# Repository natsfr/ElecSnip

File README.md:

# ElecSnip
Electronic Snippet
Storing all idea/crap/piece/circuit/thought

No interest for anyone else.

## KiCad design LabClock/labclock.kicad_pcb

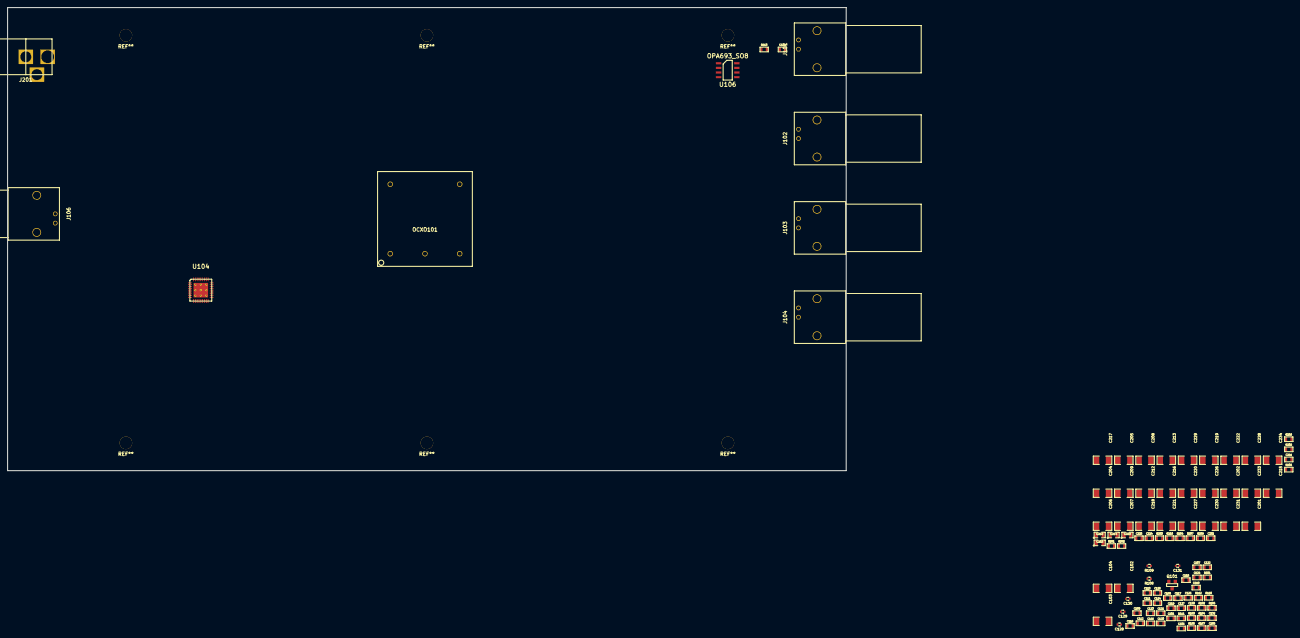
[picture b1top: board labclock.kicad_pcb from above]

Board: 2 copper layers, 230.0 x 127.0 mm, 101 parts (0 on the bottom side), 27 nets, no tracks yet.

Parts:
C101: 1uF; SM0603
C102, C103, C104, C205, C207, C208, C209, C217, C220, C221, C222: 10uF; SM1206
C105: 2uF; SM0603
C106, C109, C110, C111, C112, C116, C119, C121, C123, C124, C127, C133: 100nF; SM0603
C107, C114, C115, C118, C120, C122, C125, C126: 10pF; SM0603
C108, C113, C117: 120pF; SM0603
C128: 1nF; SM0402
C129: 100pF; SM0402
C130, C131: CAP_0402; SM0402
C132: 100pF; SM0603
C134: 10nF; SM0603
C201, C202: 1uF; SM1206
C203, C210, C214, C223: 100nF; SM0805
C204, C206, C212, C213, C215, C216, C218, C219, C226, C227, C228, C229, C230, C231, C233, C234: 10u; SM1206
C211, C224, C225, C232: 1nF; SM0603
J101, J102, J103, J104, J106: BNC; BNC_RHT-610-0048
J201: PJ-002BH-SMT; 2.1mm_DC_Jack_NEB21R_circlehole
OCXO101: NDK_NH26M26LG
Q101: BSS138; SOT23
R101, R111, R112: 1k; SM0603
R102, R103: 100; SM0603
R104: 6k; SM0603
R105, R201, R202, R204, R205, R206, R207, R209, R210: 10k; SM0603
R106: NC; SM0603
R107, R110: 500; SM0603
R108, R109: RES_0402; SM0402
R113: 50; SM0603
R203, R208: 59k; SM0603
U104: STM32F103TB-QFN36; QFN36_6x6_0.5mm
U106: OPA693_SO8; SOIC_8_150mil

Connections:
5V3_OCXO: C203.1, C204.1, C205.1, C206.1, C207.1, R203.2
5V3_PLL: C214.1, C215.1, C216.1, C217.1, C218.1, C219.1, C220.1, C230.1, C231.1, R208.2
5V_AMP: C233.1, C234.1, R111.1, U106.7
5V_OCXO: C101.1, C102.1, C104.1, C212.1, C213.1, OCXO101.5, R101.2
5V_PLL: C106.1, C107.1, C116.1, C118.1, C119.1, C120.1, C121.1, C122.1, C226.1, C228.1
+3.3V: C109.1, C110.1, C111.1, C112.1, C123.1, C124.1, C227.1, C229.1, U104.1, U104.6, U104.19, U104.27
+12V: C103.1, C202.1, C208.1, C209.1, C221.1, C222.1
/MUXOUT: R104.2, R105.1
/OCXO_PW_EN: R201.1, R204.1, R205.1, R206.1, R209.1, R210.1, U104.7
/PLLIN: C132.1, R106.2, R107.2, R110.1
/PLL_VC: C130.1, R109.1
/SINE2AMP: C117.2, C133.1, R106.1
/~PLLSEL: Q101.1, U104.8
GND: C101.2, C102.2, C103.2, C104.2, C105.2, C106.2, C107.2, C109.2, C110.2, C111.2, C112.2, C113.2, C114.1, C115.2, C116.2, C118.2, C119.2, C120.2, C121.2, C122.2, C123.2, C124.2, C125.1, C126.2, C127.2, C129.2, C130.2, C131.2, C201.2, C202.2, C203.2, C204.2, C205.2, C206.2, C207.2, C208.2, C209.2, C211.2, C212.2, C213.2, C214.2, C215.2, C216.2, C217.2, C218.2, C219.2, C220.2, C221.2, C222.2, C224.2, C225.2, C226.2, C227.2, C228.2, C229.2, C230.2, C231.2, C232.2, C233.2, C234.2, J101.2, J101.3, J102.2, J102.3, J103.2, J103.3, J104.2, J104.3, J106.2, J106.3, J201.2, J201.3, OCXO101.2, Q101.2, R103.2, R105.2, R108.2, R110.2, R112.2, R201.2, R202.2, R204.2, R205.2, R206.2, R207.2, R209.2, R210.2, U104.5, U104.18, U104.26, U104.36, U104.37, U106.4
unnamed: C105.1, R102.1
unnamed: C108.1, OCXO101.1, R107.1
unnamed: C114.2, U104.2
unnamed: C115.1, U104.3
unnamed: C128.2, J106.1
unnamed: C131.1, R109.2
unnamed: C133.2, R111.2, R112.1, U106.3
unnamed: C134.1, R113.2
unnamed: C134.2, J101.1
unnamed: C201.1, J201.1
unnamed: R113.1, U106.6
unnamed: R202.1, R203.1
unnamed: R207.1, R208.1

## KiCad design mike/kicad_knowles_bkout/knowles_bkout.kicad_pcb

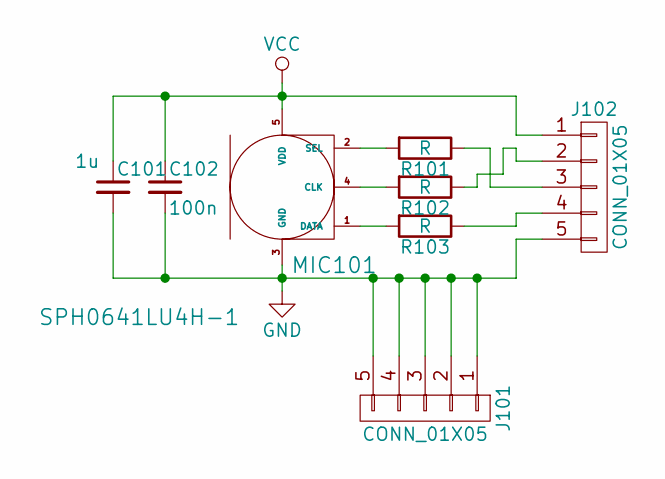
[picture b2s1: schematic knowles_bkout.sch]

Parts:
C101: 1u; C_0805_HandSoldering
C102: 100n; C_0805_HandSoldering
J101, J102: CONN_01X05; Pin_Header_Straight_1x05_Pitch2.54mm
MIC101: SPH0641LU4H-1
R101, R102, R103: R; R_0603_HandSoldering

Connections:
GND: C101.2, C102.2, J101.1, J101.2, J101.3, J101.4, J101.5, J102.5, MIC101.3 (GND)
unnamed: J102.2, R102.1
unnamed: J102.3, R101.1
unnamed: J102.4, R103.1
unnamed: MIC101.1 (DATA), R103.2
unnamed: MIC101.2 (SEL), R101.2
unnamed: MIC101.4 (CLK), R102.2
VCC: C101.1, C102.1, J102.1, MIC101.5 (VDD)

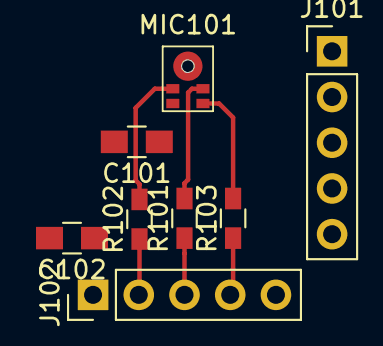
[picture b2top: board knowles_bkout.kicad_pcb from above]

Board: 2 copper layers, 8 parts (0 on the bottom side), 8 nets.

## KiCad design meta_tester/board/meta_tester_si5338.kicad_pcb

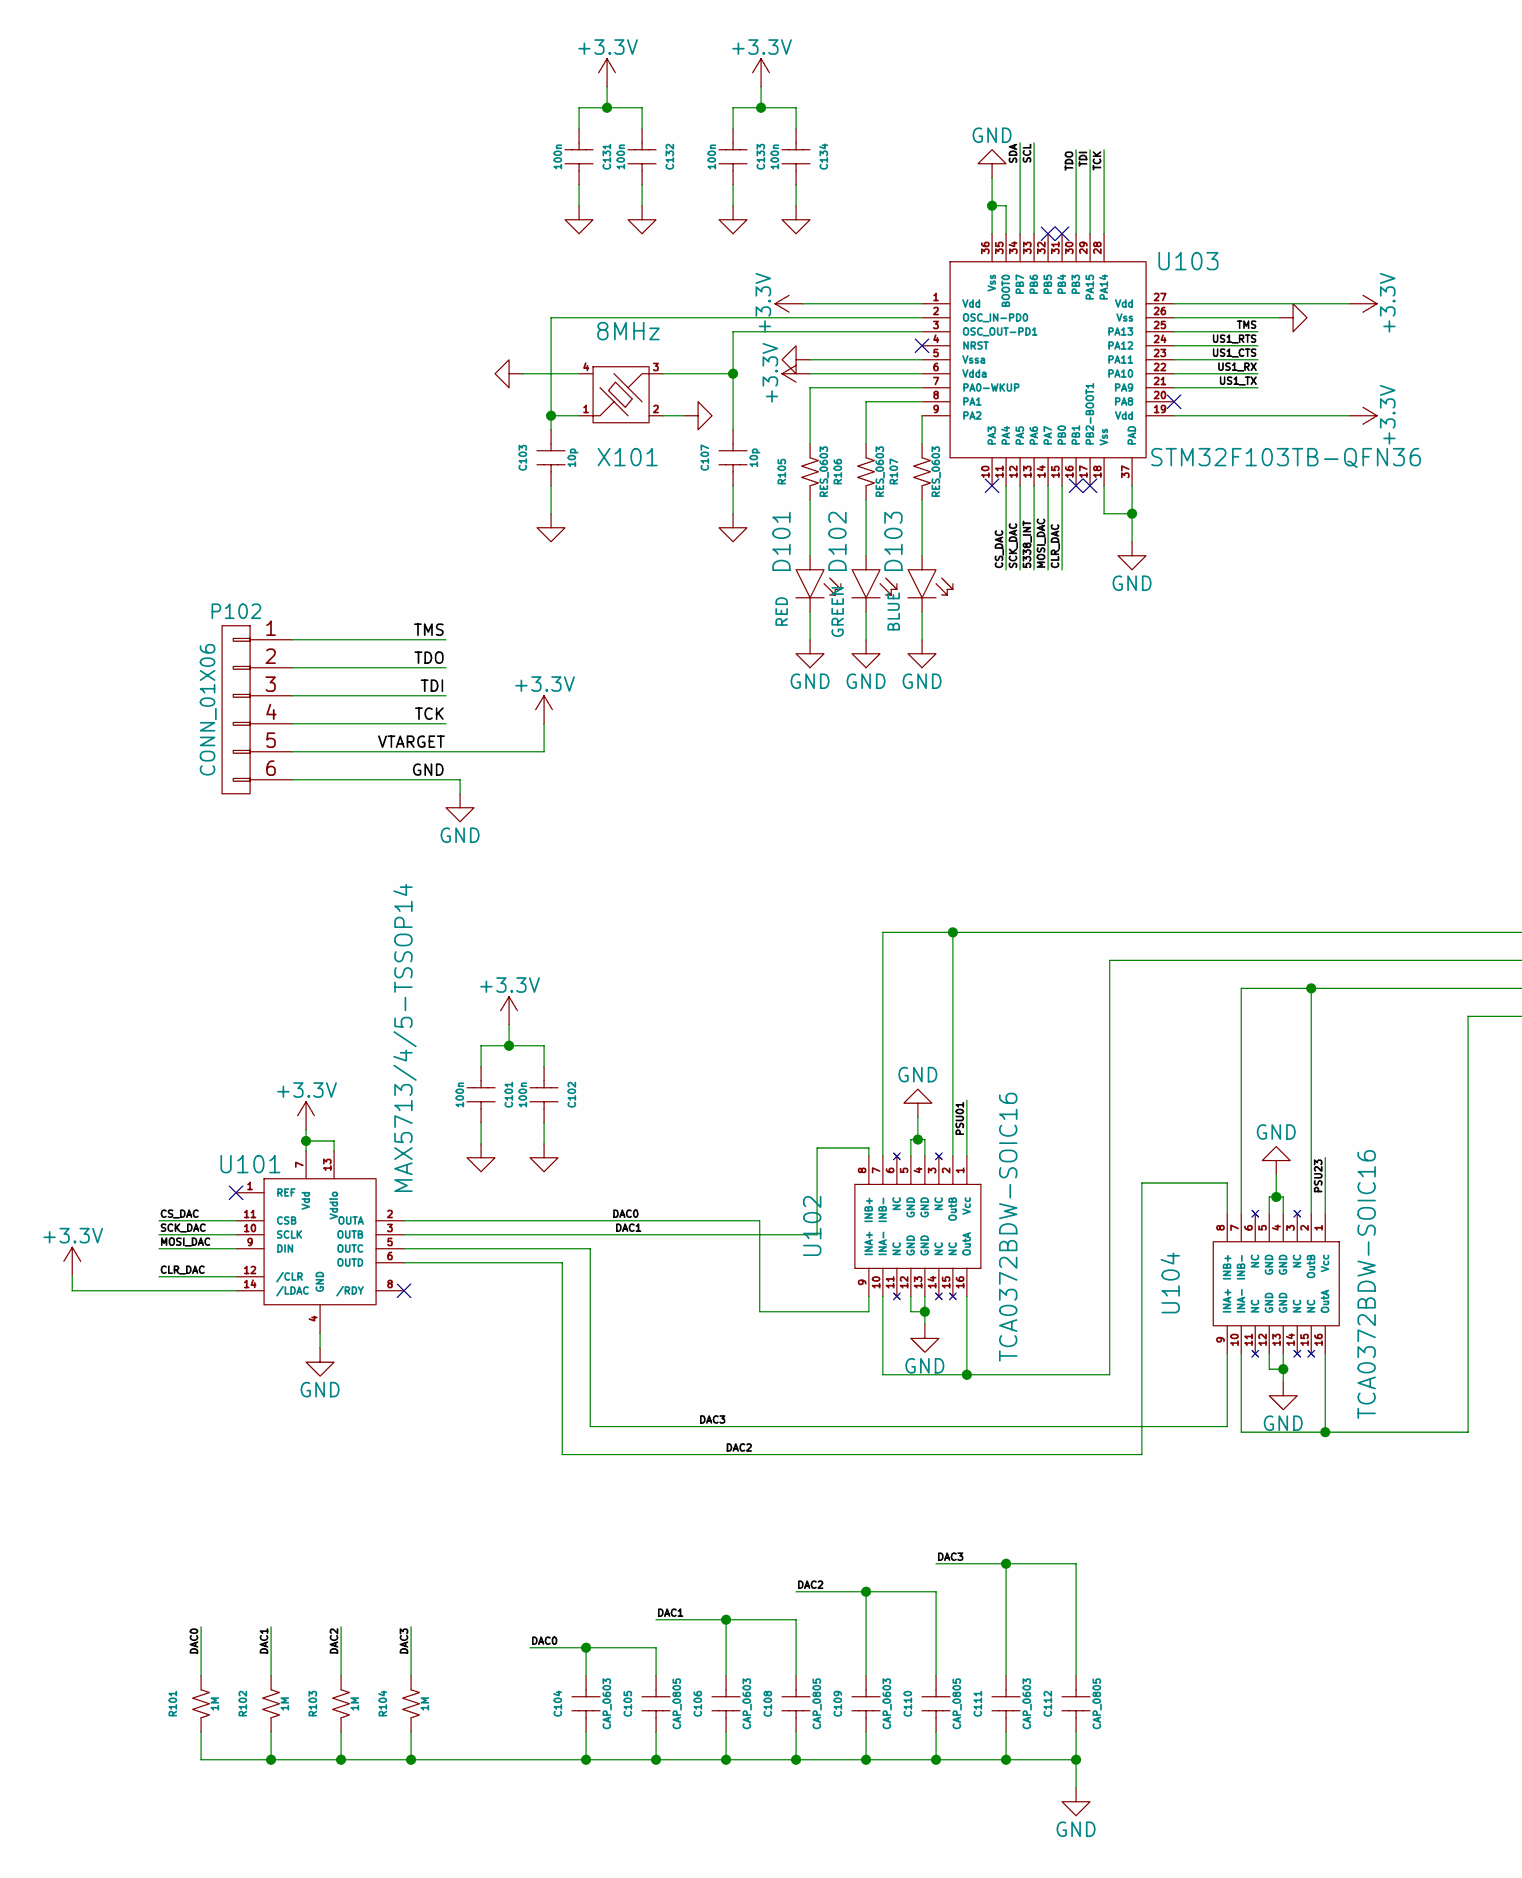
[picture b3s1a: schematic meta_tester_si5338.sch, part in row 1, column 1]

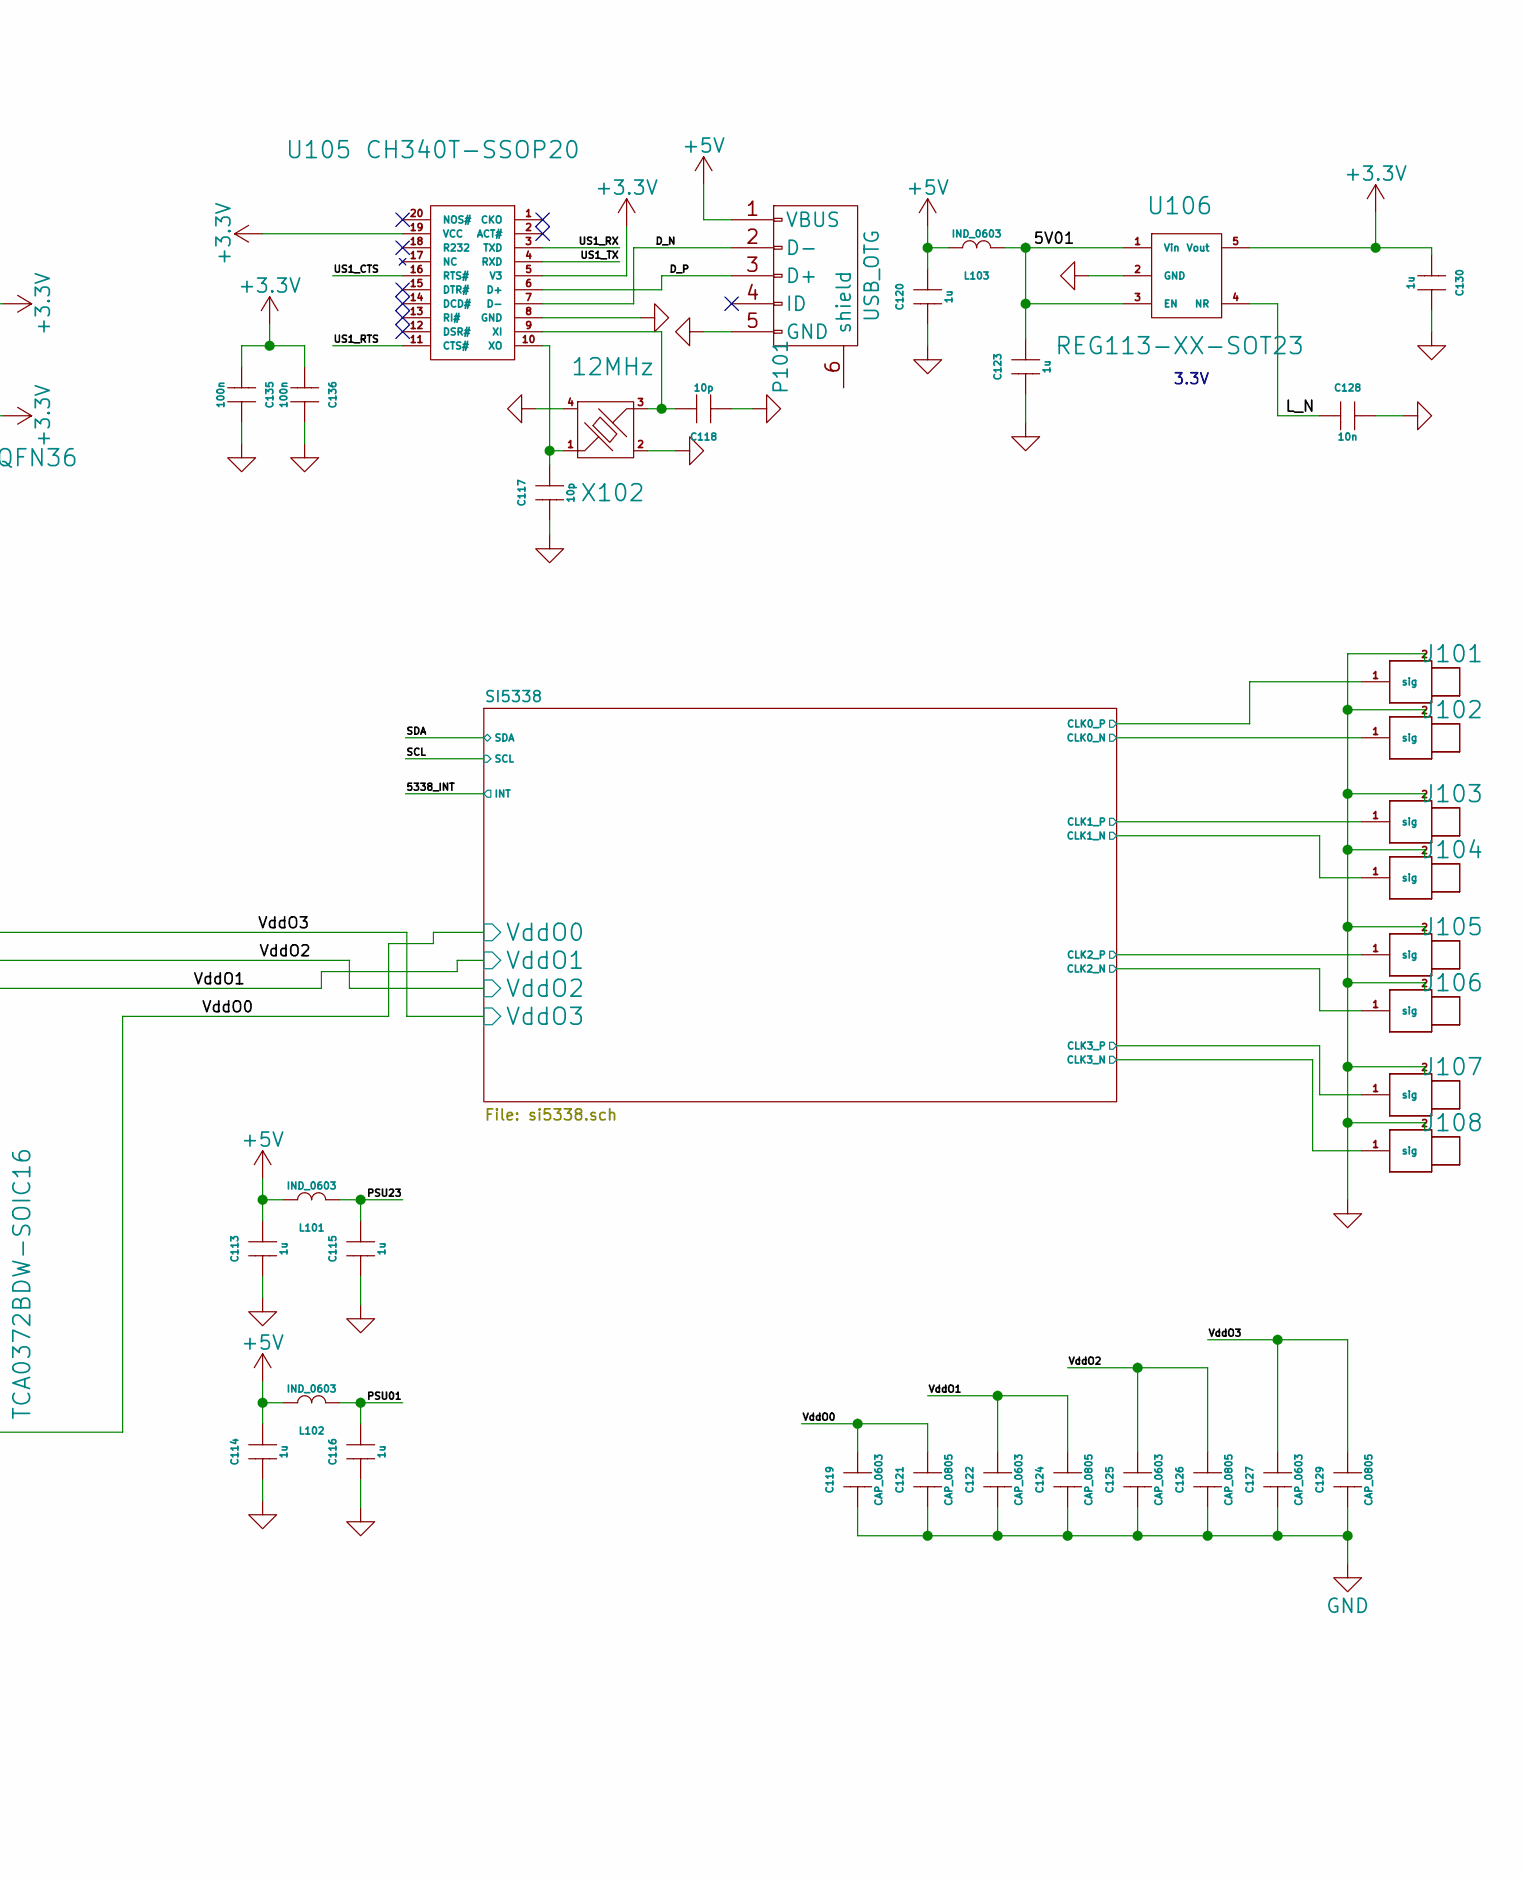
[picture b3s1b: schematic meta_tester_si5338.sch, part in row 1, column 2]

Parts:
C101, C102, C131, C132, C133, C134, C135, C136: 100n; SM0805
C103, C107, C117, C118: 10p; SM0603
C104, C106, C109, C111, C119, C122, C125, C127: CAP_0603; SM0603
C105, C108, C110, C112, C121, C124, C126, C129: CAP_0805; SM0805
C113, C114, C115, C116, C120, C123, C130: 1u; SM0805
C128: 10n; SM0603
D101: RED; LED-0603
D102: GREEN; LED-0603
D103: BLUE; LED-0603
J101, J102, J103, J104, J105, J106, J107, J108: SMA_PCB; SMA_AMP_132322
L101, L102, L103: IND_0603; SM0603
P101: USB_OTG; USB_Mini-B
P102: CONN_01X06; pin_array_6x1
R101, R102, R103, R104: 1M; SM0603
R105, R106, R107: RES_0603; SM0603
U101: MAX5713/4/5-TSSOP14; SSOP14
U102, U104: TCA0372BDW-SOIC16; SOIC-16-10.3x7.5
U103: STM32F103TB-QFN36; QFN36_6x6_0.5mm
U105: CH340T-SSOP20; SSOP-20
U106: REG113-XX-SOT23; SOT23-5
X101: 8MHz; xtal_3.2x2.5
X102: 12MHz; xtal_3.2x2.5

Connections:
+3V3: C101.2, C102.2, C130.2, C131.2, C132.2, C133.2, C134.2, C135.2, C136.2, P102.5, U101.7 (Vdd), U101.13 (Vddio), U101.14 (/LDAC), U103.1 (Vdd), U103.6 (Vdda), U103.19 (Vdd), U103.27 (Vdd), U105.5 (V3), U105.19 (VCC), U106.5 (Vout); also elsewhere on the board
+5V: C113.1, C114.1, C120.1, L101.1, L102.1, L103.1, P101.1 (VBUS)
/5V01: C123.1, L103.2, U106.1 (Vin), U106.3 (EN)
/5338_INT: U103.13 (PA6); also elsewhere on the board
/CLR_DAC: U101.12 (/CLR), U103.15 (PB0)
/CS_DAC: U101.11 (CSB), U103.11 (PA4)
/DAC0: C104.1, C105.1, R101.1, U101.2 (OUTA), U102.9 (INA+)
/DAC1: C106.1, C108.1, R102.1, U101.3 (OUTB), U102.8 (INB+)
/DAC2: C109.1, C110.1, R103.1, U101.6 (OUTD), U104.8 (INB+)
/DAC3: C111.1, C112.1, R104.1, U101.5 (OUTC), U104.9 (INA+)
/D_N: P101.2 (D-), U105.7 (D-)
/D_P: P101.3 (D+), U105.6 (D+)
/L_N: C128.2, U106.4 (NR)
/MOSI_DAC: U101.9 (DIN), U103.14 (PA7)
/PSU01: C116.1, L102.2, U102.1 (Vcc)
/PSU23: C115.1, L101.2, U104.1 (Vcc)
/SCK_DAC: U101.10 (SCLK), U103.12 (PA5)
/SCL: U103.33 (PB6); also elsewhere on the board
/SDA: U103.34 (PB7); also elsewhere on the board
/SI5338/CLK0_N: J102.1 (sig); also elsewhere on the board
/SI5338/CLK0_P: J101.1 (sig); also elsewhere on the board
/SI5338/CLK1_N: J104.1 (sig); also elsewhere on the board
/SI5338/CLK1_P: J103.1 (sig); also elsewhere on the board
/SI5338/CLK2_N: J106.1 (sig); also elsewhere on the board
/SI5338/CLK2_P: J105.1 (sig); also elsewhere on the board
/SI5338/CLK3_N: J108.1 (sig); also elsewhere on the board
/SI5338/CLK3_P: J107.1 (sig); also elsewhere on the board
/TCK: P102.4, U103.28 (PA14)
/TDI: P102.3, U103.29 (PA15)
/TDO: P102.2, U103.30 (PB3)
/TMS: P102.1, U103.25 (PA13)
/US1_CTS: U103.23 (PA11), U105.16 (RTS#)
/US1_RTS: U103.24 (PA12), U105.11 (CTS#)
/US1_RX: U103.22 (PA10), U105.3 (TXD)
/US1_TX: U103.21 (PA9), U105.4 (RXD)
/VddO0: C119.1, C121.1, U104.10 (INA-), U104.16 (OutA); also elsewhere on the board
/VddO1: C122.1, C124.1, U104.2 (OutB), U104.7 (INB-); also elsewhere on the board
/VddO2: C125.1, C126.1, U102.10 (INA-), U102.16 (OutA); also elsewhere on the board
/VddO3: C127.1, C129.1, U102.2 (OutB), U102.7 (INB-); also elsewhere on the board
GND: C101.1, C102.1, C103.2, C104.2, C105.2, C106.2, C107.2, C108.2, C109.2, C110.2, C111.2, C112.2, C113.2, C114.2, C115.2, C116.2, C117.2, C118.2, C119.2, C120.2, C121.2, C122.2, C123.2, C124.2, C125.2, C126.2, C127.2, C128.1, C129.2, C130.1, C131.1, C132.1, C133.1, C134.1, C135.1, C136.1, D101.K, D102.K, D103.K, J101.2, J102.2, J103.2, J104.2, J105.2, J106.2, J107.2, J108.2, P101.5 (GND), P102.6, R101.2, R102.2, R103.2, R104.2, U101.4 (GND), U102.4 (GND), U102.5 (GND), U102.12 (GND), U102.13 (GND), U103.5 (Vssa), U103.18 (Vss), U103.26 (Vss), U103.35 (BOOT0), U103.36 (Vss), U103.37 (PAD), U104.4 (GND), U104.5 (GND), U104.12 (GND), U104.13 (GND), U105.8 (GND), U106.2 (GND), X101.2, X101.4, X102.2, X102.4; also elsewhere on the board
unnamed: C103.1, U103.2 (OSC_IN-PD0), X101.1
unnamed: C107.1, U103.3 (OSC_OUT-PD1), X101.3
unnamed: C117.1, U105.10 (XO), X102.1
unnamed: C118.1, U105.9 (XI), X102.3
unnamed: D101.A, R105.2
unnamed: D102.A, R106.2
unnamed: D103.A, R107.2
unnamed: R105.1, U103.7 (PA0-WKUP)
unnamed: R106.1, U103.8 (PA1)
unnamed: R107.1, U103.9 (PA2)

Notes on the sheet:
3.3V

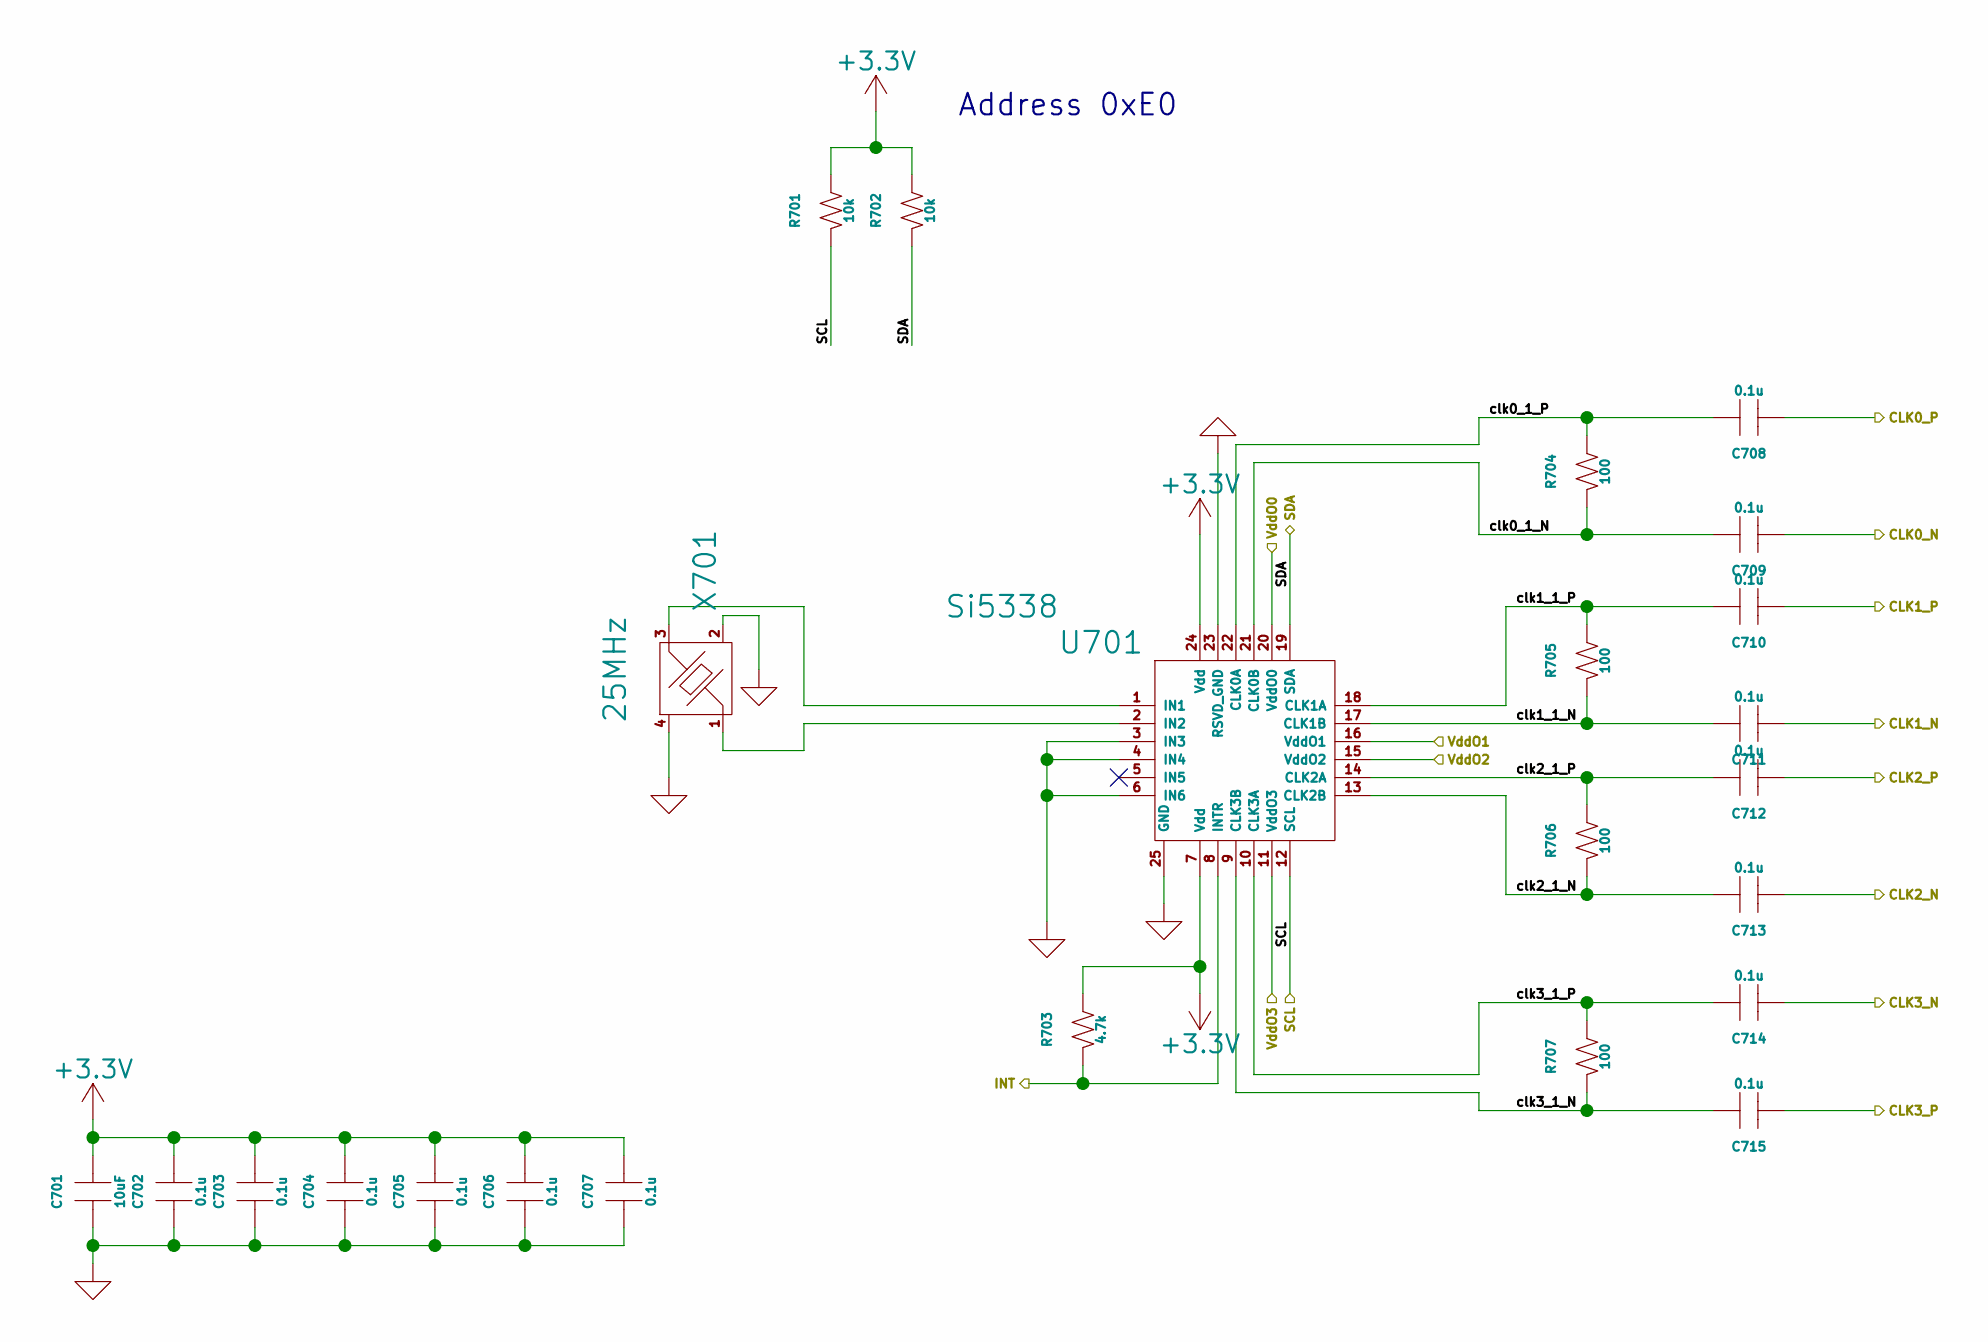
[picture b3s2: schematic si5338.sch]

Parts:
C701: 10uF; SM0805
C702, C703, C704, C705, C706, C707, C708, C709, C710, C711, C712, C713, C714, C715: 0.1u; SM0402
R701, R702: 10k; SM0402
R703: 4.7k; SM0402
R704, R705, R706, R707: 100; SM0402
U701: Si5338; QFN24_4x4_9vias
X701: 25MHz; xtal_3.2x2.5

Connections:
+3V3: C701.1, C702.1, C703.1, C704.1, C705.1, C706.1, C707.1, R701.1, R702.1, R703.1, U701.7 (Vdd), U701.24 (Vdd); also elsewhere on the board
/5338_INT: R703.2, U701.8 (INTR); also elsewhere on the board
/SCL: R701.2, U701.12 (SCL); also elsewhere on the board
/SDA: R702.2, U701.19 (SDA); also elsewhere on the board
/SI5338/CLK0_N: C709.2; also elsewhere on the board
/SI5338/CLK0_P: C708.2; also elsewhere on the board
/SI5338/CLK1_N: C711.2; also elsewhere on the board
/SI5338/CLK1_P: C710.2; also elsewhere on the board
/SI5338/CLK2_N: C713.2; also elsewhere on the board
/SI5338/CLK2_P: C712.2; also elsewhere on the board
/SI5338/CLK3_N: C714.2; also elsewhere on the board
/SI5338/CLK3_P: C715.2; also elsewhere on the board
/SI5338/clk0_1_N: C709.1, R704.2, U701.21 (CLK0B)
/SI5338/clk0_1_P: C708.1, R704.1, U701.22 (CLK0A)
/SI5338/clk1_1_N: C711.1, R705.2, U701.17 (CLK1B)
/SI5338/clk1_1_P: C710.1, R705.1, U701.18 (CLK1A)
/SI5338/clk2_1_N: C713.1, R706.2, U701.13 (CLK2B)
/SI5338/clk2_1_P: C712.1, R706.1, U701.14 (CLK2A)
/SI5338/clk3_1_N: C715.1, R707.2, U701.9 (CLK3B)
/SI5338/clk3_1_P: C714.1, R707.1, U701.10 (CLK3A)
/VddO0: U701.20 (VddO0); also elsewhere on the board
/VddO1: U701.16 (VddO1); also elsewhere on the board
/VddO2: U701.15 (VddO2); also elsewhere on the board
/VddO3: U701.11 (VddO3); also elsewhere on the board
GND: C701.2, C702.2, C703.2, C704.2, C705.2, C706.2, C707.2, U701.3 (IN3), U701.4 (IN4), U701.6 (IN6), U701.23 (RSVD_GND), U701.25 (GND), X701.2, X701.4; also elsewhere on the board
unnamed: U701.1 (IN1), X701.3
unnamed: U701.2 (IN2), X701.1

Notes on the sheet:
Address 0xE0

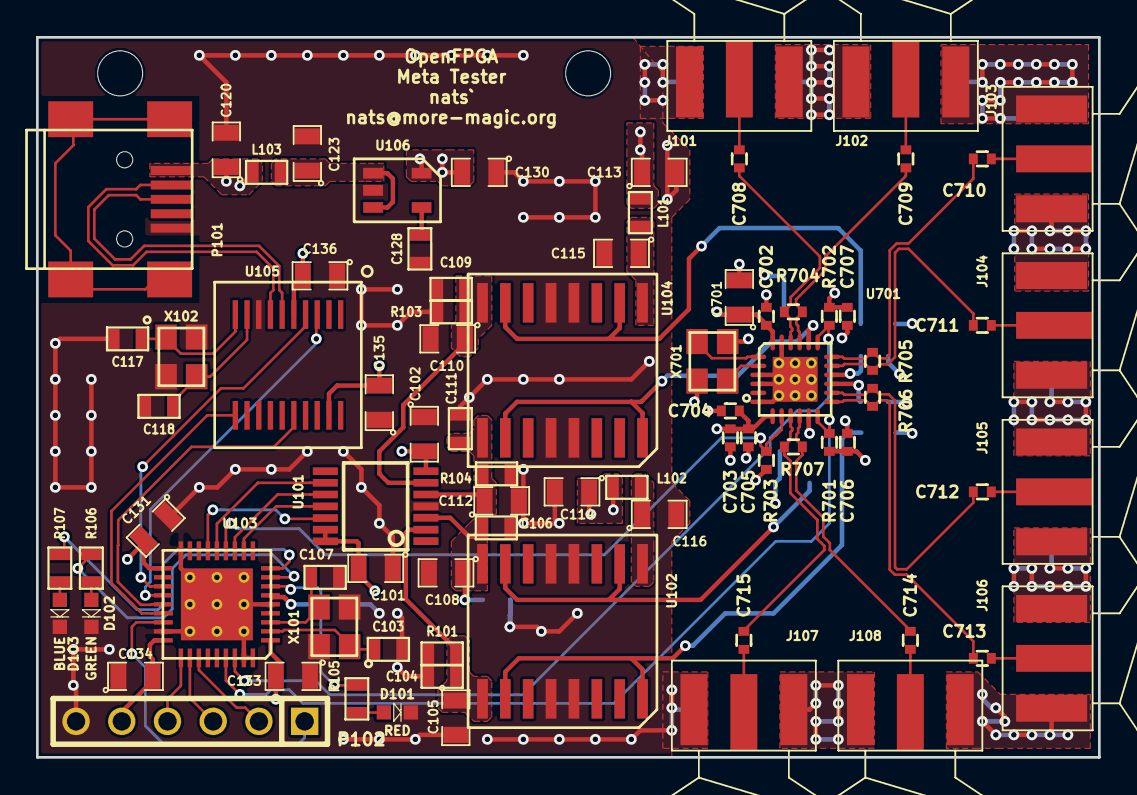
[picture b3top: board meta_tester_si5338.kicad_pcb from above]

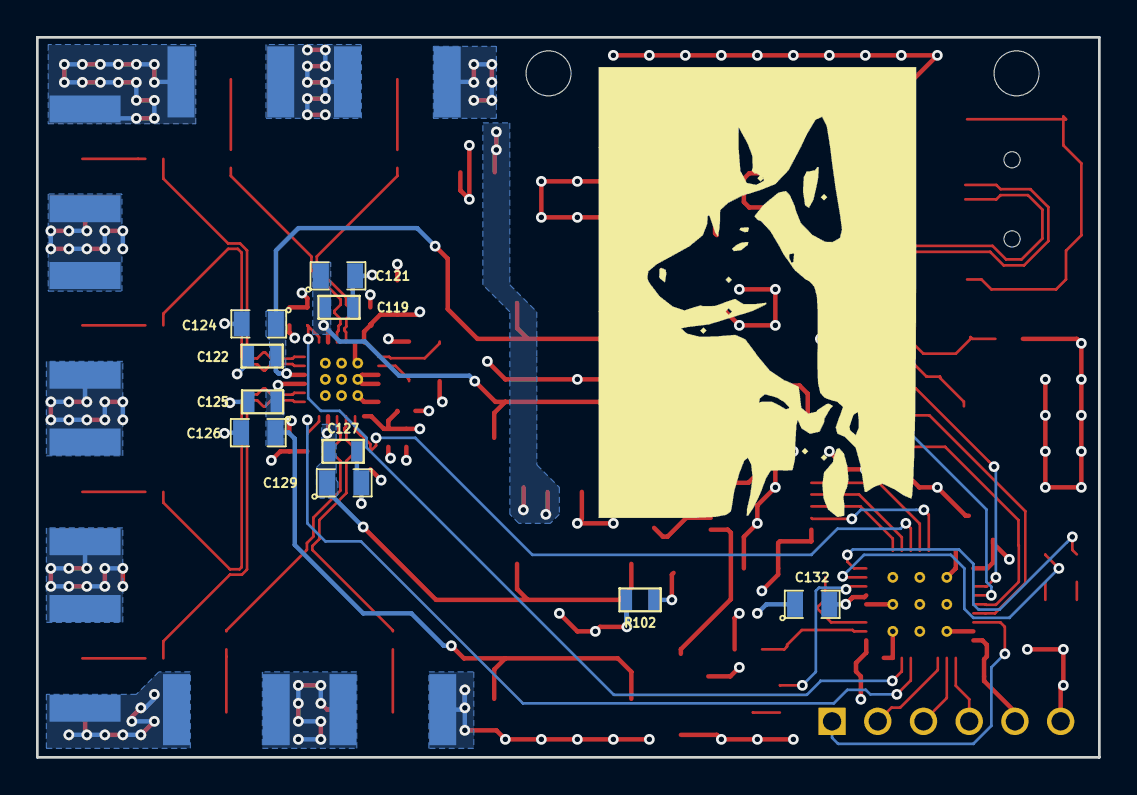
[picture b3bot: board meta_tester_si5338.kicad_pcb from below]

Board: 4 copper layers, 59.0 x 40.0 mm, 91 parts (10 on the bottom side), 60 nets.

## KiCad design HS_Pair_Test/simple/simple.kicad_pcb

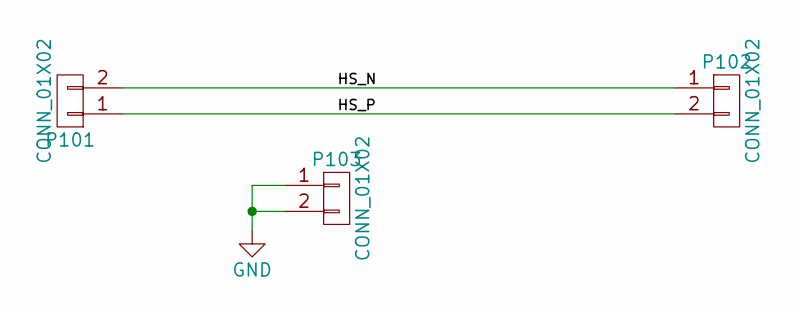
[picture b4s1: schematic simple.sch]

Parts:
P101, P102: CONN_01X02; TEST_01x02_05mm
P103: CONN_01X02; pin_array_2x1

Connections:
/HS_N: P101.2, P102.1
/HS_P: P101.1, P102.2
GND: P103.1, P103.2

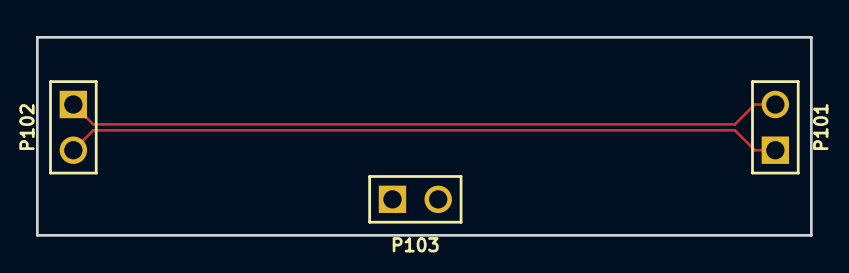
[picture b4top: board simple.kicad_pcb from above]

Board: 2 copper layers, 43.0 x 11.0 mm, 3 parts (0 on the bottom side), 3 nets.

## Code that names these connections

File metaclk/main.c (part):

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    DEV_STATIC_RES_IRQ(0, STM32_IRQ_USART1, DEV_IRQ_SENSE_HIGH_LEVEL, 0, 0x1),
    
    DEV_STATIC_RES_DEV_PARAM("iomux", "/gpio"),
    DEV_STATIC_RES_IOMUX("tx", 0, /* PA9 */ 0*16+9, 0, 0),
    DEV_STATIC_RES_IOMUX("rx", 0, /* PA10 */ 0*16+10, 0, 0),

    DEV_STATIC_RES_UART(115200, 8, DEV_UART_PARITY_NONE, 1, 0, 0));

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    DEV_STATIC_RES_IRQ(0, STM32_IRQ_SPI1, DEV_IRQ_SENSE_RISING_EDGE, 0, 0x1),
    
    DEV_STATIC_RES_DEV_IOMUX("/gpio"),
    DEV_STATIC_RES_IOMUX("clk", 0, 0*16+5 /* PA5 */, 0 /* no remap */, 0),
    //DEV_STATIC_RES_IOMUX("miso", 0, 0*16+6 /* PA6 */, 0 /* no remap */, 0), Used as a GPIO Input
    DEV_STATIC_RES_IOMUX("mosi", 0, 0*16+7 /* PA7 */, 0 /* no remap */, 0)
    );

DEV_DECLARE_STATIC(timer4_dev, "timer4", 0, stm32_timer_drv,
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    DEV_STATIC_RES_IRQ(0, STM32_IRQ_TIM4, DEV_IRQ_SENSE_HIGH_LEVEL, 0, 0x1),
    );

#define CS_DAC              4 //PA4
#define INT_5338            6 //PA6
#define CLR_DAC             16 //PB0
#define RED_LED             0 //PA0
#define GREEN_LED           1 //PA1
#define ORG_LED             2 //PA2

#define SDA                 23 //PB7
#define SCL                 22 //PB6

DEV_DECLARE_STATIC(i2c_dev, "i2c0", 0, i2c_bitbang_drv,
                   DEV_STATIC_RES_DEV_TIMER("timer* rtc*"),
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    dev_gpio_out(&d_gpio, ORG_LED, 0);
    
    // Init DAC GPIO
    dev_gpio_mode(&d_gpio, CLR_DAC, DEV_PIN_PUSHPULL);
    
    dev_gpio_out(&d_gpio, CLR_DAC, 1);
    
    // Init SPI
    dev_gpio_mode(&d_gpio, CS_DAC, DEV_PIN_PUSHPULL);
    
    dev_gpio_out(&d_gpio, CS_DAC, 1);
    
    struct dev_spi_ctrl_config_s cfg = {
        .ck_mode = DEV_SPI_CK_MODE_0,
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    
    DEVICE_OP(&dac_spi, config, &cfg);
    
    dac_spi_write(&dac_spi, CS_DAC, (const uint8_t*)"\x40\x0F\x00", 3); // Power all dac
    dac_spi_write(&dac_spi, CS_DAC, (const uint8_t*)"\x75\x00\x00", 3); // Set all ref to internal 2.5V
    dac_spi_write(&dac_spi, CS_DAC, (const uint8_t*)"\x2F\xFF\x00", 3); // Set all dac to maximum
    
    // test pll init
    for(uint16_t i = 0; i < 351; i++) {
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
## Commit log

2015-09-06 adding ltspice modele of basic amplifier to be verified in circuit
2015-09-10 adding HIGH SPEED test
2015-09-10 changed the simple example with a SMT connector
2016-12-20 starting 1A led driver
2016-12-20 making new mosfet lib
2016-12-20 schematic finished
2016-12-24 need to finish layout for the 1A regulator
2017-01-02 almost finished led drvier
2017-01-02 finished driver, need to order stencil
2017-02-20 starting tester for metastability
2017-02-21 added hierarchical pin
2017-02-22 Adding OPAMP
2017-02-23 starting layout
2017-02-23 reversed CTS/RTS
2017-02-24 adding jtag connector
2017-02-24 starting placing components
2017-02-25 working on pcb
2017-02-25 starting simulation for sampling head + layout for clock board
2017-02-26 pcb'
2017-02-26 blabla
2017-02-27 working on layout
2017-02-27 almost finished pcb
2017-02-28 finished pcb
2017-02-28 save before generating gerber
2017-03-01 valid gerber
2017-03-05 modified bridge for demo
2017-03-13 adding automatcher script for bjt amplifier
2017-03-13 Added mutekh project for the meta tester
2017-03-14 adding python calculator
2017-03-14 removing huge simulations files
2017-03-14 adding si5338 doc and bat15 model
2017-03-15 added register map
2017-03-15 trying to startup PLL
2017-03-19 adding SCM calculation
2017-03-22 need to fix gain calculation, there are weird shit
2017-03-22 working phase shifting function
2017-03-22 merge
2017-03-22 weird git problem
2017-03-22 cleaned conflict crap
2017-03-22 changed log to log10
2017-03-23 working SCM and basic gain calculation
2017-03-24 Adding line to ignore noise parameter from infineon file
2017-03-24 matching the BFP420 amplifier
2017-03-25 changed text and verified error in book
2017-03-26 need to fix ref2z function
2017-03-26 working ref2z
2017-04-09 added step counter
2017-04-09 working eye diagram python script
2017-04-10 Added utils functions for impedance calculation
2017-07-17 devboard for knowles mic
2017-07-18 added leo footprint
2018-03-19 begins of labclock
2018-03-19 fixed stuff
